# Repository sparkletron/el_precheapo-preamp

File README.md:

# EL PRECHEAPO PREAMP

---
    AUTHOR: John Convertino   
    
    DATE: 2021.01.04   
    
    DETAILS: Cheap preamplifier   
---

### DIRECTORY
#### models
3D models
* back_panel.stl        - Back panel for preamplifier
* front_panel.stl       - Front panel for preamplifier
* side.stl              - Right/Left side for preamplifier
* top.stl               - Top for preamplifier
* bot.stl               - Bot for preamplifier
* el_precheapo.FCStd    - FreeCAD model of circuit board.
* el_precheapo.step     - FreeCAD model of circuit board in STEP format.

#### schematic
KiCad Schematic and PCBS
* el_precheapo.pro - Main KiCAD project file

#### docs
Articles and datasheets used for the project.
* jrc4556.pdf - Opamp datasheet

#### sim
Simulation and Spec Write Ups
* N/A

### PARTS LIST
* BACK PANEL... 1
* FRONT PANEL... 1
* SIDE... 2
* TOP... 1
* BOTTOM... 1
* PCB... 1
* SCHEMATIC PARTS LIST: Reference, Quantity, Value, Footprint, Datasheet
    * C1 C2 ,2,"1000uF","Capacitor_THT:CP_Radial_D12.5mm_P5.00mm","~"
    * C10 C9 C20 C19 ,4,"22pf","Capacitor_THT:C_Disc_D5.0mm_W2.5mm_P5.00mm","~"
    * C11 C14 ,2,"0.1UF","Capacitor_THT:C_Disc_D4.7mm_W2.5mm_P5.00mm","~"
    * C3 C4 ,2,"47uF","Capacitor_THT:CP_Radial_D8.0mm_P3.80mm","~"
    * C5 C6 C22 C21 ,4,"1UF","Capacitor_THT:C_Rect_L16.5mm_W7.0mm_P15.00mm_MKT","~"
    * C7 C8 C17 C18 C12 C13 C15 C16 ,8,"10UF","Capacitor_THT:CP_Radial_D8.0mm_P3.80mm","~"
    * D1 ,1,"D_Bridge_+AA-","Diode_THT:Diode_Bridge_15.1x15.1x6.3mm_P10.9mm","~"
    * F1 ,1,"0.5 AMP","Connector_Molex:Molex_KK-396_A-41791-0002_1x02_P3.96mm_Vertical","~"
    * F2 F3 ,2,"0.1 AMP","Connector_PinHeader_2.54mm:PinHeader_1x02_P2.54mm_Vertical","~"
    * H1 H2 H3 H4 ,4,"MountingHole","MountingHole:MountingHole_3mm_Pad","~"
    * J1 J2 ,2,"Conn_01x03","Connector_Molex:Molex_KK-254_AE-6410-03A_1x03_P2.54mm_Vertical","~"
    * J3 ,1,"Conn_01x02","Connector_Molex:Molex_KK-396_A-41791-0002_1x02_P3.96mm_Vertical","~"
    * R16 R15 ,2,"15K","Resistor_THT:R_Axial_DIN0207_L6.3mm_D2.5mm_P10.16mm_Horizontal","~"
    * R17 R18 ,2,"100K","Resistor_THT:R_Axial_DIN0207_L6.3mm_D2.5mm_P10.16mm_Horizontal","~"
    * R19 R20 ,2,"100","Resistor_THT:R_Axial_DIN0207_L6.3mm_D2.5mm_P10.16mm_Horizontal","~"
    * R2 R1 ,2,"1M","Resistor_THT:R_Axial_DIN0207_L6.3mm_D2.5mm_P10.16mm_Horizontal","~"
    * R3 R4 R12 R11 R13 R14 ,6,"10K","Resistor_THT:R_Axial_DIN0207_L6.3mm_D2.5mm_P10.16mm_Horizontal","~"
    * R6 R5 ,2,"22K","Resistor_THT:R_Axial_DIN0207_L6.3mm_D2.5mm_P10.16mm_Horizontal","~"
    * R8 R7 ,2,"150","Resistor_THT:R_Axial_DIN0207_L6.3mm_D2.5mm_P10.16mm_Horizontal","~"
    * R9 R10 ,2,"1K5","Resistor_THT:R_Axial_DIN0207_L6.3mm_D2.5mm_P10.16mm_Horizontal","~"
    * RV2 RV1 RV4 RV3 ,4,"R_POT","Connector_Molex:Molex_KK-254_AE-6410-03A_1x03_P2.54mm_Vertical","~"
    * SW1 ,1,"SW_SPST","Connector_Molex:Molex_KK-396_A-41791-0002_1x02_P3.96mm_Vertical","~"
    * T1 ,1,"Transformer_1P_SS","Connector_Molex:Molex_KK-396_A-41791-0005_1x05_P3.96mm_Vertical","~"
    * U1 ,1,"L7809","Package_TO_SOT_THT:TO-220-3_Vertical",
    * U2 ,1,"L7909","Package_TO_SOT_THT:TO-220-3_Vertical",
    * U3 U4 ,2,"NE5532","Package_DIP:DIP-8_W7.62mm_LongPads","http://www.ti.com/lit/ds/symlink/ne5532.pdf"

### BUILD HELP
* 3D print all parts with ABS at 101% to deal with shrinkage. Otherwise, good luck! I used parts I had around for the pots. Pulled from some 1970's stereo. No idea if you can find something that matches the case exactly.
* Balance pot is 5k
* Volume pot is 50k
* The pots can be changed as long as they have a 10x ratio. Also alter the resistors to countour the pots steps to your liking.

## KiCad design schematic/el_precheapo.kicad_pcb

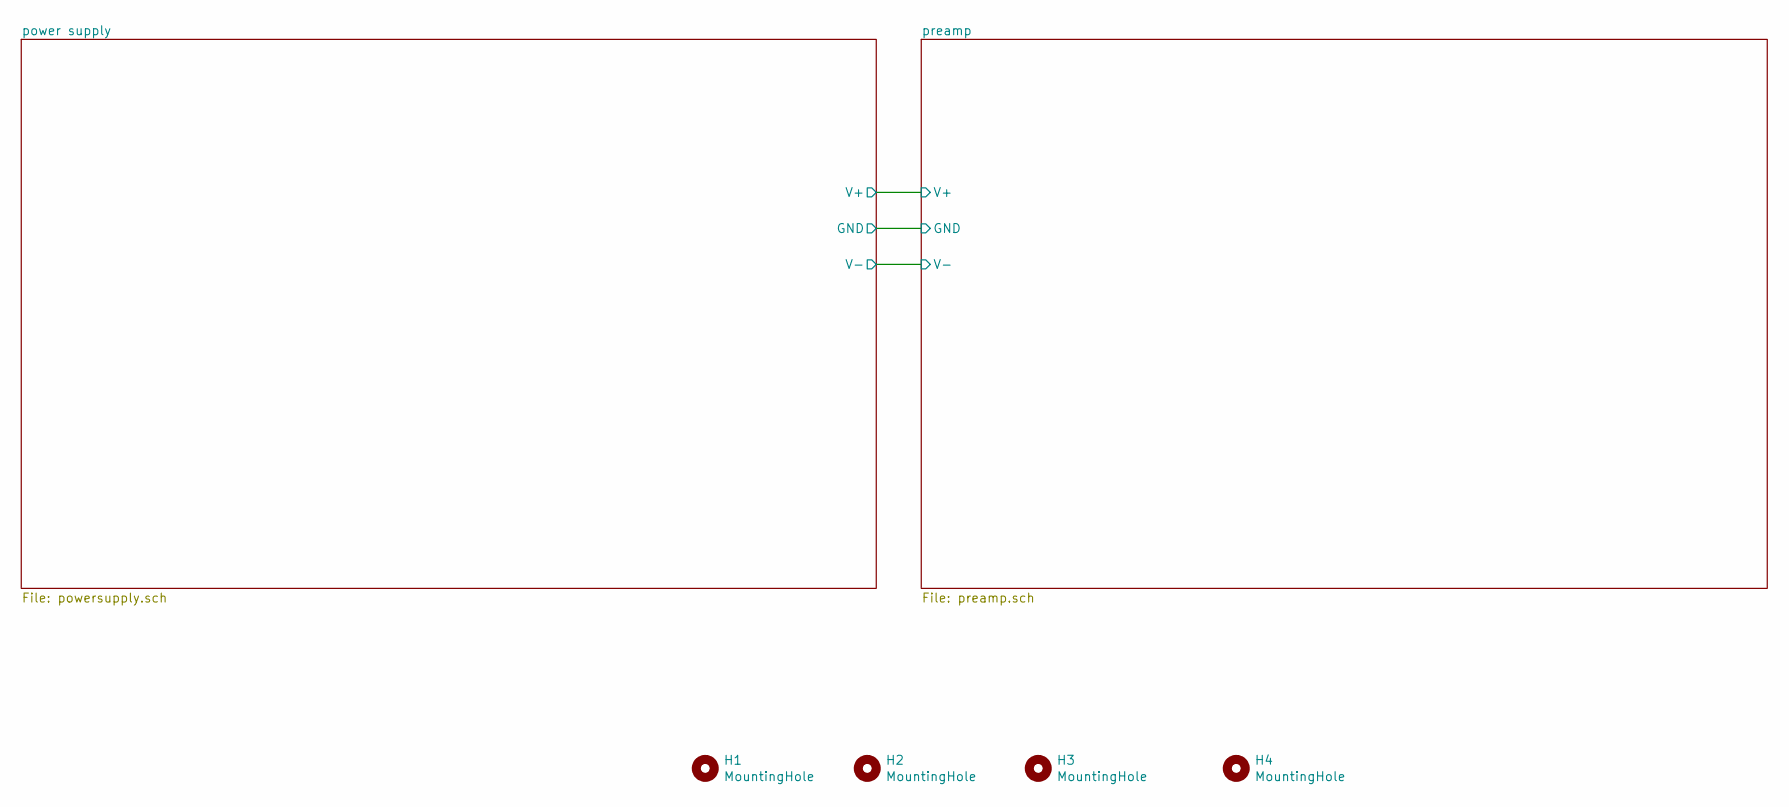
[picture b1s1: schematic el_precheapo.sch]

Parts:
H1, H2, H3, H4: MountingHole; MountingHole_3mm_Pad

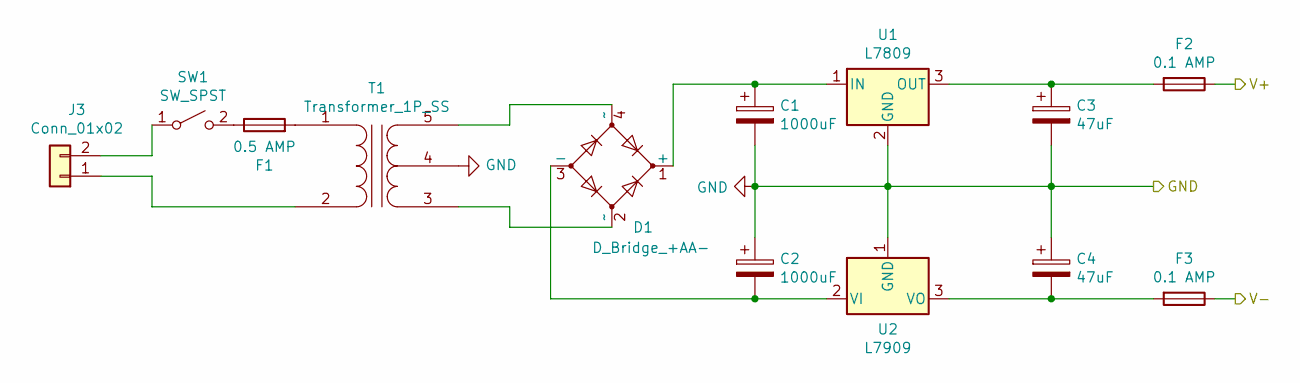
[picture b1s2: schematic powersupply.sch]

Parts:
C1, C2: 1000uF; CP_Radial_D12.5mm_P5.00mm
C3, C4: 47uF; CP_Radial_D8.0mm_P3.80mm
D1: D_Bridge_+AA-; Diode_Bridge_15.1x15.1x6.3mm_P10.9mm
F1: 0.5 AMP; Molex_KK-396_A-41791-0002_1x02_P3.96mm_Vertical
F2, F3: 0.1 AMP; PinHeader_1x02_P2.54mm_Vertical
J3: Conn_01x02; Molex_KK-396_A-41791-0002_1x02_P3.96mm_Vertical
SW1: SW_SPST; Molex_KK-396_A-41791-0002_1x02_P3.96mm_Vertical
T1: Transformer_1P_SS; Molex_KK-396_A-41791-0005_1x05_P3.96mm_Vertical
U1: L7809; TO-220-3_Vertical
U2: L7909; TO-220-3_Vertical

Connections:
/power supply/V+: F2.1; also elsewhere on the board
/power supply/V-: F3.1; also elsewhere on the board
GND: C1.2, C2.1, C3.2, C4.1, T1.4 (SC), U1.2 (GND), U2.1 (GND); also elsewhere on the board
unnamed: C1.1, D1.1 (+), U1.1 (IN)
unnamed: C2.2, D1.3 (-), U2.2 (VI)
unnamed: C3.1, F2.2, U1.3 (OUT)
unnamed: C4.2, F3.2, U2.3 (VO)
unnamed: D1.2 (~~), T1.3 (SA)
unnamed: D1.4 (~~), T1.5 (SB)
unnamed: F1.1, SW1.2 (B)
unnamed: F1.2, T1.1 (AA)
unnamed: J3.1, T1.2 (AB)
unnamed: J3.2, SW1.1 (A)

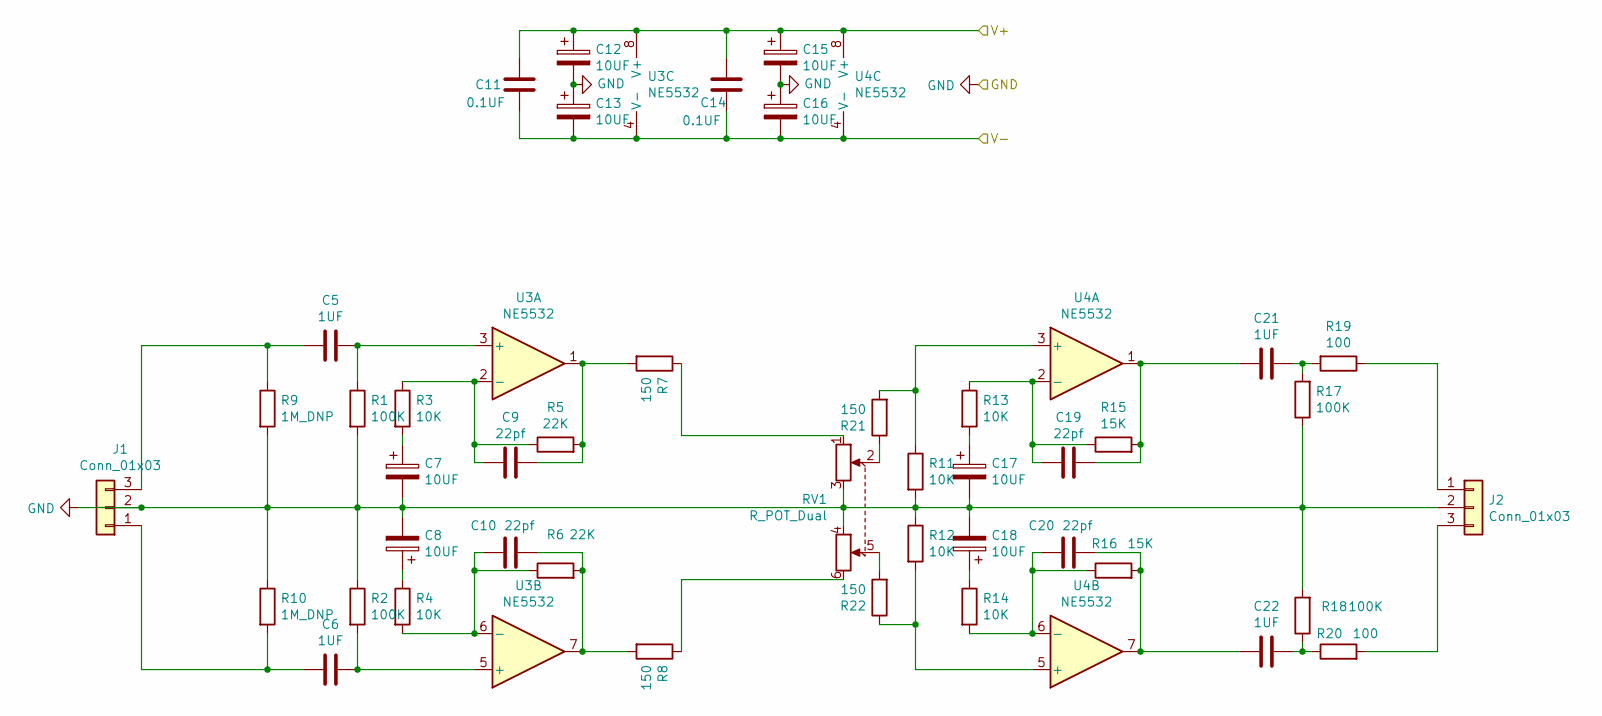
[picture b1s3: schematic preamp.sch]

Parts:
C5, C6, C21, C22: 1UF; C_Rect_L16.5mm_W7.0mm_P15.00mm_MKT
C7, C8, C12, C13, C15, C16, C17, C18: 10UF; CP_Radial_D8.0mm_P3.80mm
C9, C10, C19, C20: 22pf; C_Disc_D5.0mm_W2.5mm_P5.00mm
C11, C14: 0.1UF; C_Disc_D4.7mm_W2.5mm_P5.00mm
J1, J2: Conn_01x03; Molex_KK-254_AE-6410-03A_1x03_P2.54mm_Vertical
R1, R2, R17, R18: 100K; R_Axial_DIN0207_L6.3mm_D2.5mm_P10.16mm_Horizontal
R3, R4, R11, R12, R13, R14: 10K; R_Axial_DIN0207_L6.3mm_D2.5mm_P10.16mm_Horizontal
R5, R6: 22K; R_Axial_DIN0207_L6.3mm_D2.5mm_P10.16mm_Horizontal
R7, R8, R21, R22: 150; R_Axial_DIN0207_L6.3mm_D2.5mm_P10.16mm_Horizontal
R9, R10: 1M_DNP; R_Axial_DIN0207_L6.3mm_D2.5mm_P10.16mm_Horizontal
R15, R16: 15K; R_Axial_DIN0207_L6.3mm_D2.5mm_P10.16mm_Horizontal
R19, R20: 100; R_Axial_DIN0207_L6.3mm_D2.5mm_P10.16mm_Horizontal
RV1: R_POT_Dual; Potentiometer_Alpha_RD902F-40-00D_Dual_Vertical
U3, U4: NE5532; DIP-8_W7.62mm_LongPads

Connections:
/power supply/V+: C11.2, C12.1, C14.2, C15.1, U3.8 (V+), U4.8 (V+); also elsewhere on the board
/power supply/V-: C11.1, C13.2, C14.1, C16.2, U3.4 (V-), U4.4 (V-); also elsewhere on the board
GND: C7.2, C8.2, C12.2, C13.1, C15.2, C16.1, C17.2, C18.2, J1.2, J2.2, R1.2, R2.1, R9.2, R10.1, R11.2, R12.1, R17.1, R18.2, RV1.3, RV1.4; also elsewhere on the board
unnamed: C5.1, R1.1, U3.3 (+)
unnamed: C5.2, J1.3, R9.1
unnamed: C6.1, R2.2, U3.5 (+)
unnamed: C6.2, J1.1, R10.2
unnamed: C7.1, R3.2
unnamed: C8.1, R4.1
unnamed: C9.1, R5.2, R7.2, U3.1
unnamed: C9.2, R3.1, R5.1, U3.2 (-)
unnamed: C10.1, R6.2, R8.2, U3.7
unnamed: C10.2, R4.2, R6.1, U3.6 (-)
unnamed: C17.1, R13.2
unnamed: C18.1, R14.1
unnamed: C19.1, C21.2, R15.2, U4.1
unnamed: C19.2, R13.1, R15.1, U4.2 (-)
unnamed: C20.1, C22.2, R16.2, U4.7
unnamed: C20.2, R14.2, R16.1, U4.6 (-)
unnamed: C21.1, R17.2, R19.2
unnamed: C22.1, R18.1, R20.1
unnamed: J2.1, R19.1
unnamed: J2.3, R20.2
unnamed: R7.1, RV1.1
unnamed: R8.1, RV1.6
unnamed: R11.1, R21.2, U4.3 (+)
unnamed: R12.2, R22.1, U4.5 (+)
unnamed: R21.1, RV1.2
unnamed: R22.2, RV1.5

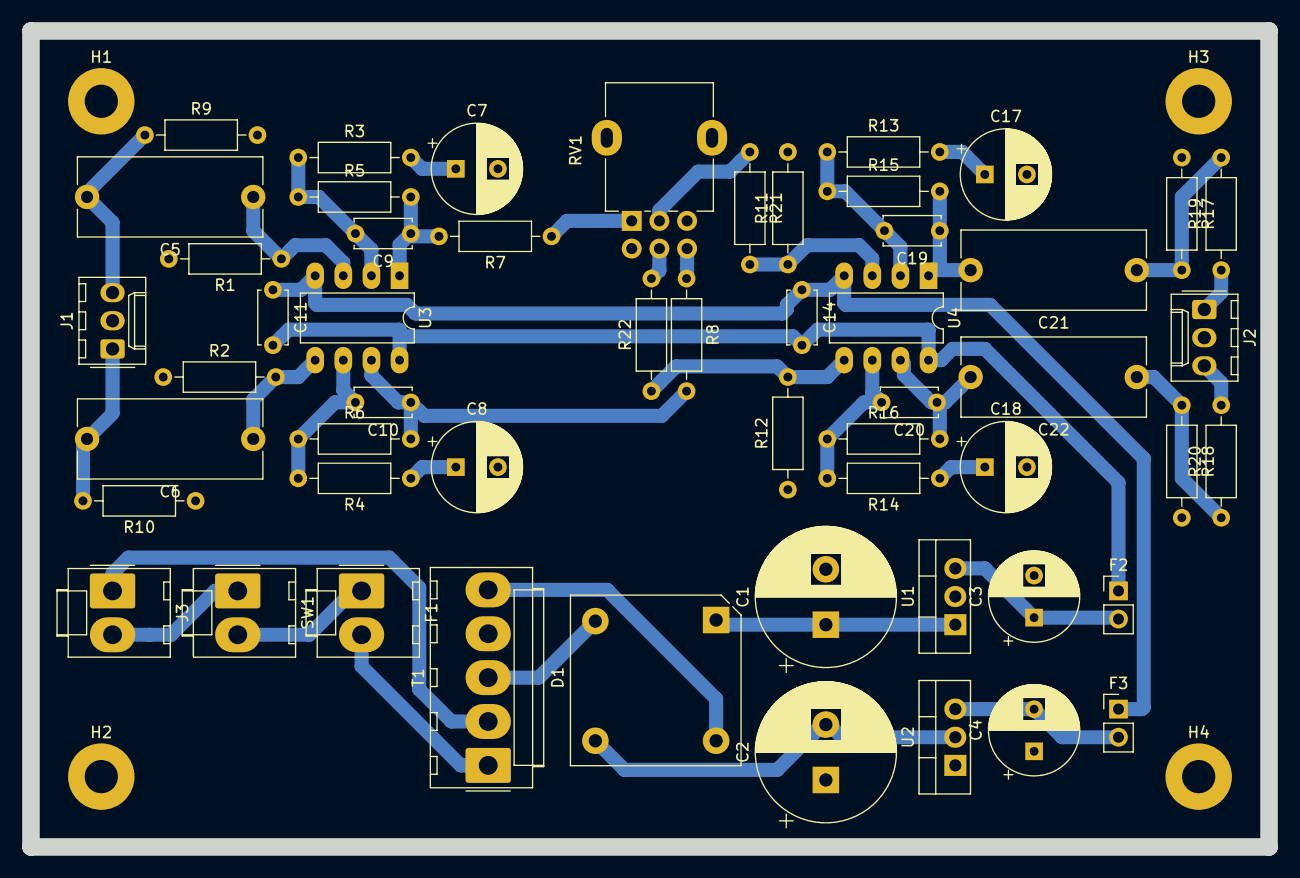
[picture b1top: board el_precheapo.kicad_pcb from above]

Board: 2 copper layers, 111.8 x 73.7 mm, 58 parts (0 on the bottom side), 39 nets.

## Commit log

2021-05-19 inital commit
2021-05-20 updated readme with parts and build tips
2021-08-22 update to a single volume board mnt version.
2024-03-25 fixed for github
